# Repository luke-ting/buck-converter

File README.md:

# Synchronous Buck Converter

Custom synchronous buck converter PCB designed in KiCad and simulated in LTspice.

## Specifications

- Input voltage: 12 V
- Output voltage: 5-9 V
- Maximum output current: 5 A
- Topology: synchronous buck
- PCB: 2-layer
- Tools: KiCad, LTspice

## Project Overview

This project was created to learn PCB design and power electronics through the design, simulation, layout, assembly, and testing of a synchronous buck converter.

## Design Process

1. Defined electrical requirements
2. Designed the power stage
3. Simulated the circuit in LTspice
4. Created the schematic in KiCad. (credit: GreatScott!)
5. Selected components and footprints
6. Designed the PCB layout
7. Ran ERC and DRC
8. Ordered the PCB
9. Currently assembly and testing voltage regulation, ripple, and efficiency

## PCB

Images and design details will be added here.

## Results

Testing results will be added soon.

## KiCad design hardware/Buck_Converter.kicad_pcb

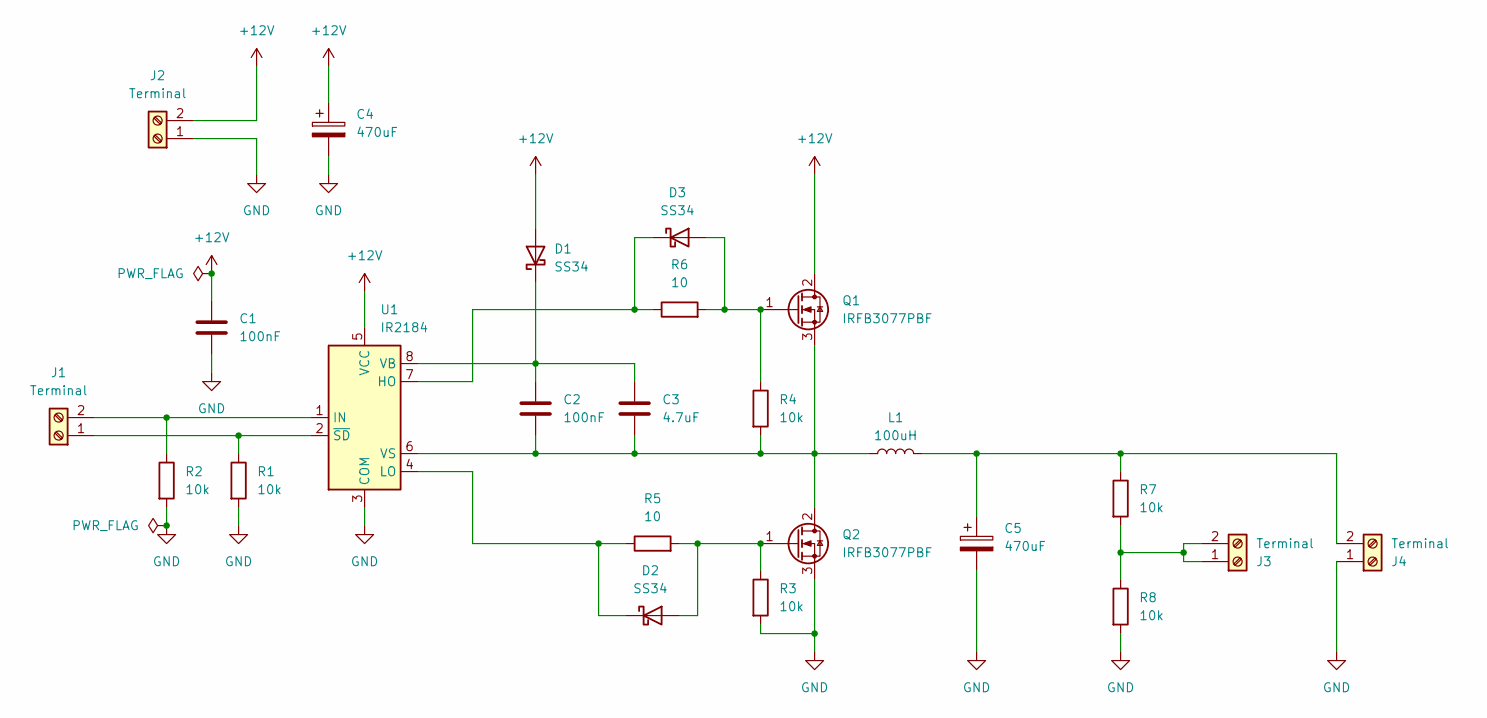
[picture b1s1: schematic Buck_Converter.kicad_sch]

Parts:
C1, C2: 100nF; C_0805_2012Metric_Pad1.18x1.45mm_HandSolder; MPN CL21B104KBCNNNC
C3: 4.7uF; C_0805_2012Metric_Pad1.18x1.45mm_HandSolder; MPN CC0805KKX5R8BB475
C4, C5: 470uF; CP_Radial_D10.0mm_P5.00mm; MPN UHE1V471MPD
D1, D2, D3: SS34; D_SMA_Handsoldering; MPN MBRS340T3G
J1, J2, J3, J4: Terminal; TerminalBlock_Phoenix_MKDS-1,5-2-5.08_1x02_P5.08mm_Horizont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; MPN 1715721
L1: 100uH; L_Toroid_Vertical_L22.4mm_W10.2mm_P7.90mm_Vishay_TJ4; MPN 2100HT-101-V-RC
Q1, Q2: IRFB3077PBF; TO-220-3_Vertical; MPN IRFB3077PBF
R1, R2, R3, R4, R7, R8: 10k; R_0805_2012Metric_Pad1.20x1.40mm_HandSolder; MPN RC0805JR-0710KL
R5, R6: 10; R_0805_2012Metric_Pad1.20x1.40mm_HandSolder; MPN RC0805JR-0710RL
U1: IR2184; SOIC-8_3.9x4.9mm_P1.27mm; MPN IR2184SPBF

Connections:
+12V: C1.1, C4.1, D1.2 (A), J2.2, Q1.2 (D), U1.5 (VCC)
GND: C1.2, C4.2, C5.2, J2.1, J4.1, Q2.3 (S), R1.2, R2.2, R3.2, R8.2, U1.3 (COM)
unnamed: C2.1, C3.1, D1.1 (K), U1.8 (VB)
unnamed: D2.2 (A), Q2.1 (G), R3.1, R5.2
unnamed: D2.1 (K), R5.1, U1.4 (LO)
unnamed: D3.2 (A), Q1.1 (G), R4.1, R6.2
unnamed: D3.1 (K), R6.1, U1.7 (HO)
unnamed: J1.1, R1.1, U1.2 (~SD)
unnamed: J1.2, R2.1, U1.1 (IN)
unnamed: J3.1, J3.2, R7.2, R8.1
unnamed: C5.1, J4.2, L1.2, R7.1
unnamed: C2.2, C3.2, L1.1, Q1.3 (S), Q2.2 (D), R4.2, U1.6 (VS)

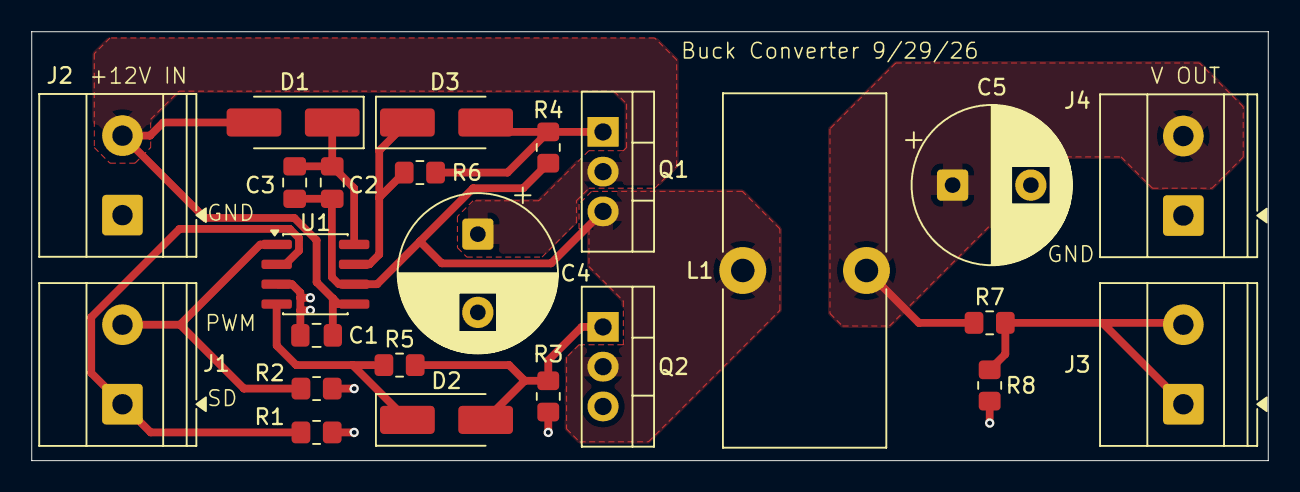
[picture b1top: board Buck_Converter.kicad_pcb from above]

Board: 2 copper layers, 79.0 x 27.4 mm, 24 parts (0 on the bottom side), 12 nets.
